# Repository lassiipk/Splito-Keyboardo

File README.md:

# Saim-Chan
Splito Keboardo, Made with ♥ by SAIM.  Named as サイムちゃん (Saimu-chan).

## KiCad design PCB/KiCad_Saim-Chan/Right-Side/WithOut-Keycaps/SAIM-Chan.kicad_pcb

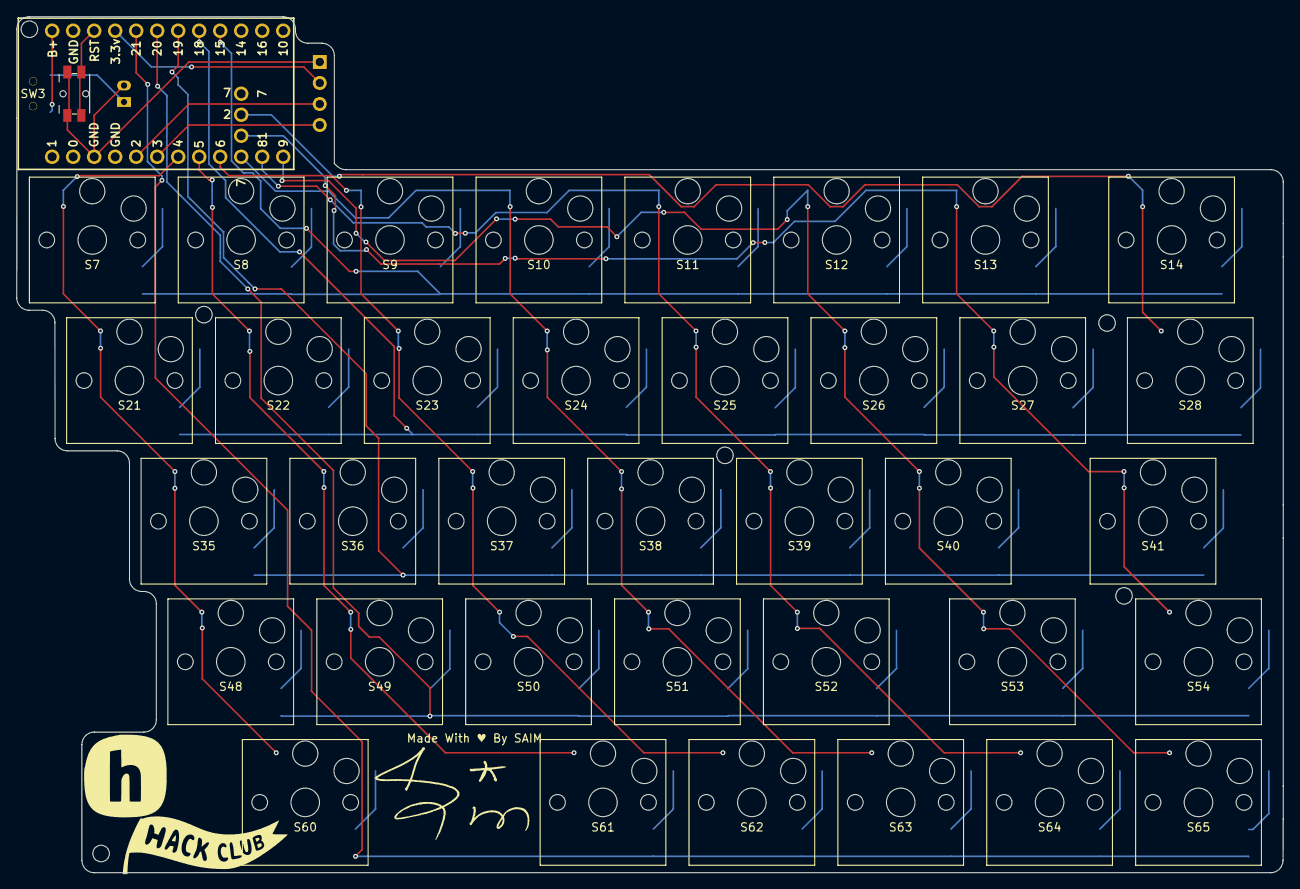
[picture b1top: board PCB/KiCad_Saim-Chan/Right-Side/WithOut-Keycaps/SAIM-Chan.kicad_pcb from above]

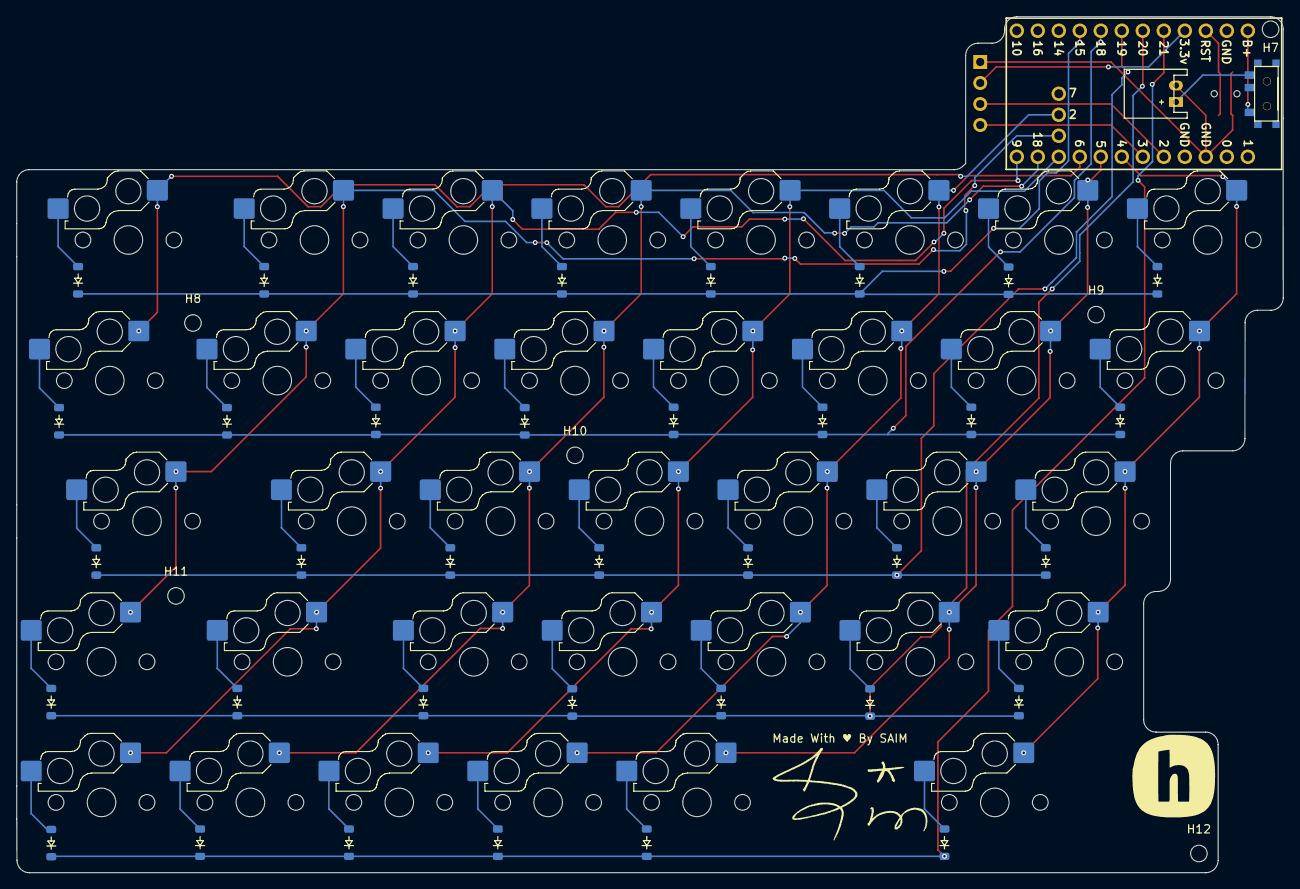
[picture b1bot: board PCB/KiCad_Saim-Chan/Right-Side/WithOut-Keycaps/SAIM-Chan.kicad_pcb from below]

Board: 2 copper layers, 153.1 x 103.5 mm, 83 parts (42 on the bottom side), 56 nets.

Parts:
D7, D8, D9, D10, D11, D12, D13, D14, D21, D22, D23, D24, D25, D26, D27, D28, D35, D36, D37, D38, D39, D40, D41, D48, D49, D50, D51, D52, D53, D54, D60, D61, D62, D63, D64, D65: Diode_SOD-123
Display_2: OLED_128x32
H7, H8, H9, H10, H11, H12: MountingScrew; MountingHole_2mm
J2: Conn_01x02; JST_PH_S2B-PH-K_02x2.00mm_Angled
S7, S8, S9, S10, S11, S12, S13, S21, S22, S23, S24, S25, S26, S27, S35, S36, S37, S38, S39, S40, S48, S49, S50, S51, S52, S54, S61, S62, S63, S64, S65: Hotswap_Choc_V1_1.00u
S14, S53: Hotswap_Choc_V1_1.50u
S28: Hotswap_Choc_V1_1.25u
S41: Hotswap_Choc_V1_1.75u
S60: Hotswap_Choc_V1_3.00u
SW2: SW_SPDT_312; SPDT_C128955
SW3: Switch; Panasonic_EVQPUL_EVQPUC
U2: Nice_Nano_V2

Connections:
COL0_R: S7.1, S21.1, S35.1, S48.1, S60.1, U2.7 (4)
COL1_R: S8.1, S22.1, S36.1, S49.1, S61.1, U2.8 (5)
COL2_R: S9.1, S23.1, S37.1, S50.1, S62.1, U2.9 (6)
COL3_R: S10.1, S24.1, S38.1, S51.1, S63.1, U2.10 (7)
COL4_R: S11.1, S25.1, S39.1, S52.1, S64.1, U2.11 (8)
COL5_R: S12.1, S26.1, S40.1, S53.1, S65.1, U2.12 (9)
COL6_R: S13.1, S27.1, S41.1, S54.1, U2.25 (1)
COL7_R: S14.1, S28.1, U2.26 (2)
GND_R: Display_2.1 (GND), J2.2, SW3.1, U2.3 (GND)
unnamed: D7.2 (A), S7.2
unnamed: D8.2 (A), S8.2
unnamed: D9.2 (A), S9.2
unnamed: D10.2 (A), S10.2
unnamed: D11.2 (A), S11.2
unnamed: D12.2 (A), S12.2
unnamed: D13.2 (A), S13.2
unnamed: D14.2 (A), S14.2
unnamed: D21.2 (A), S21.2
unnamed: D22.2 (A), S22.2
unnamed: D23.2 (A), S23.2
unnamed: D24.2 (A), S24.2
unnamed: D25.2 (A), S25.2
unnamed: D26.2 (A), S26.2
unnamed: D27.2 (A), S27.2
unnamed: D28.2 (A), S28.2
unnamed: D35.2 (A), S35.2
unnamed: D36.2 (A), S36.2
unnamed: D37.2 (A), S37.2
unnamed: D38.2 (A), S38.2
unnamed: D39.2 (A), S39.2
unnamed: D40.2 (A), S40.2
unnamed: D41.2 (A), S41.2
unnamed: D48.2 (A), S48.2
unnamed: D49.2 (A), S49.2
unnamed: D50.2 (A), S50.2
unnamed: D51.2 (A), S51.2
unnamed: D52.2 (A), S52.2
unnamed: D53.2 (A), S53.2
unnamed: D54.2 (A), S54.2
unnamed: D60.2 (A), S60.2
unnamed: D61.2 (A), S61.2
unnamed: D62.2 (A), S62.2
unnamed: D63.2 (A), S63.2
unnamed: D64.2 (A), S64.2
unnamed: D65.2 (A), S65.2
unnamed: J2.1, SW2.3 (A)
unnamed: SW2.1 (B), U2.24 (B+)
ROW0_R: D7.1 (K), D8.1 (K), D9.1 (K), D10.1 (K), D11.1 (K), D12.1 (K), D13.1 (K), D14.1 (K), U2.16 (15)
ROW1_R: D21.1 (K), D22.1 (K), D23.1 (K), D24.1 (K), D25.1 (K), D26.1 (K), D27.1 (K), D28.1 (K), U2.17 (18)
ROW2_R: D35.1 (K), D36.1 (K), D37.1 (K), D38.1 (K), D39.1 (K), D40.1 (K), D41.1 (K), U2.18 (19)
ROW3_R: D48.1 (K), D49.1 (K), D50.1 (K), D51.1 (K), D52.1 (K), D53.1 (K), D54.1 (K), U2.19 (20)
ROW4_R: D60.1 (K), D61.1 (K), D62.1 (K), D63.1 (K), D64.1 (K), D65.1 (K), U2.20 (21)
RST_R: SW3.2, U2.22 (RST)
SCL_R: Display_2.3 (SCL), U2.5 (2)
SDA_R: Display_2.4 (SDA), U2.6 (3)
VCC_R: Display_2.2 (VCC), U2.21 (3.3v)

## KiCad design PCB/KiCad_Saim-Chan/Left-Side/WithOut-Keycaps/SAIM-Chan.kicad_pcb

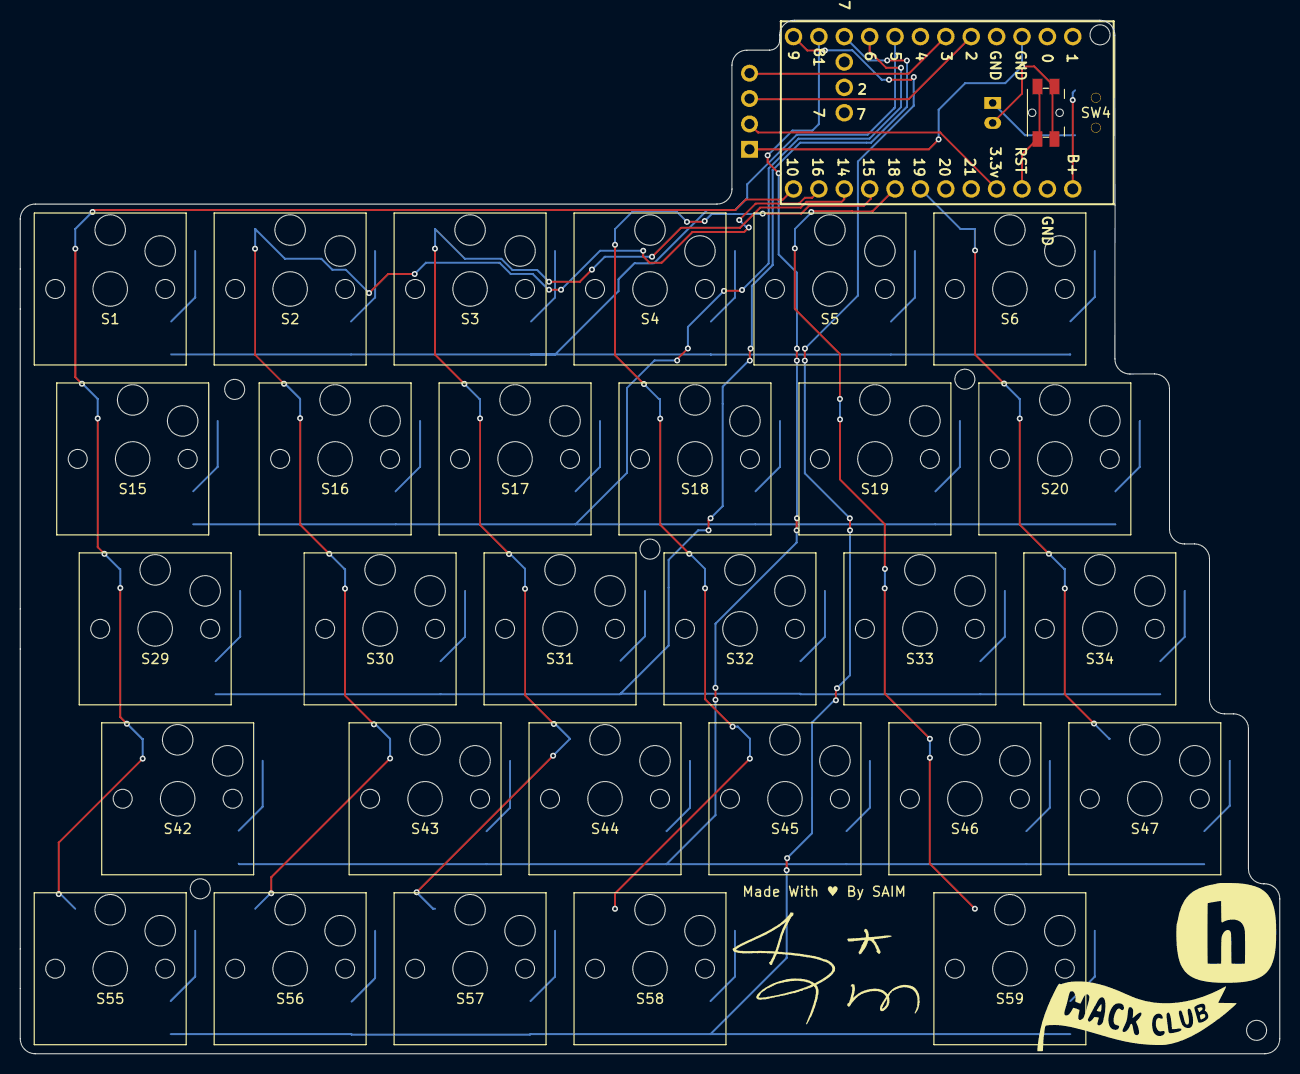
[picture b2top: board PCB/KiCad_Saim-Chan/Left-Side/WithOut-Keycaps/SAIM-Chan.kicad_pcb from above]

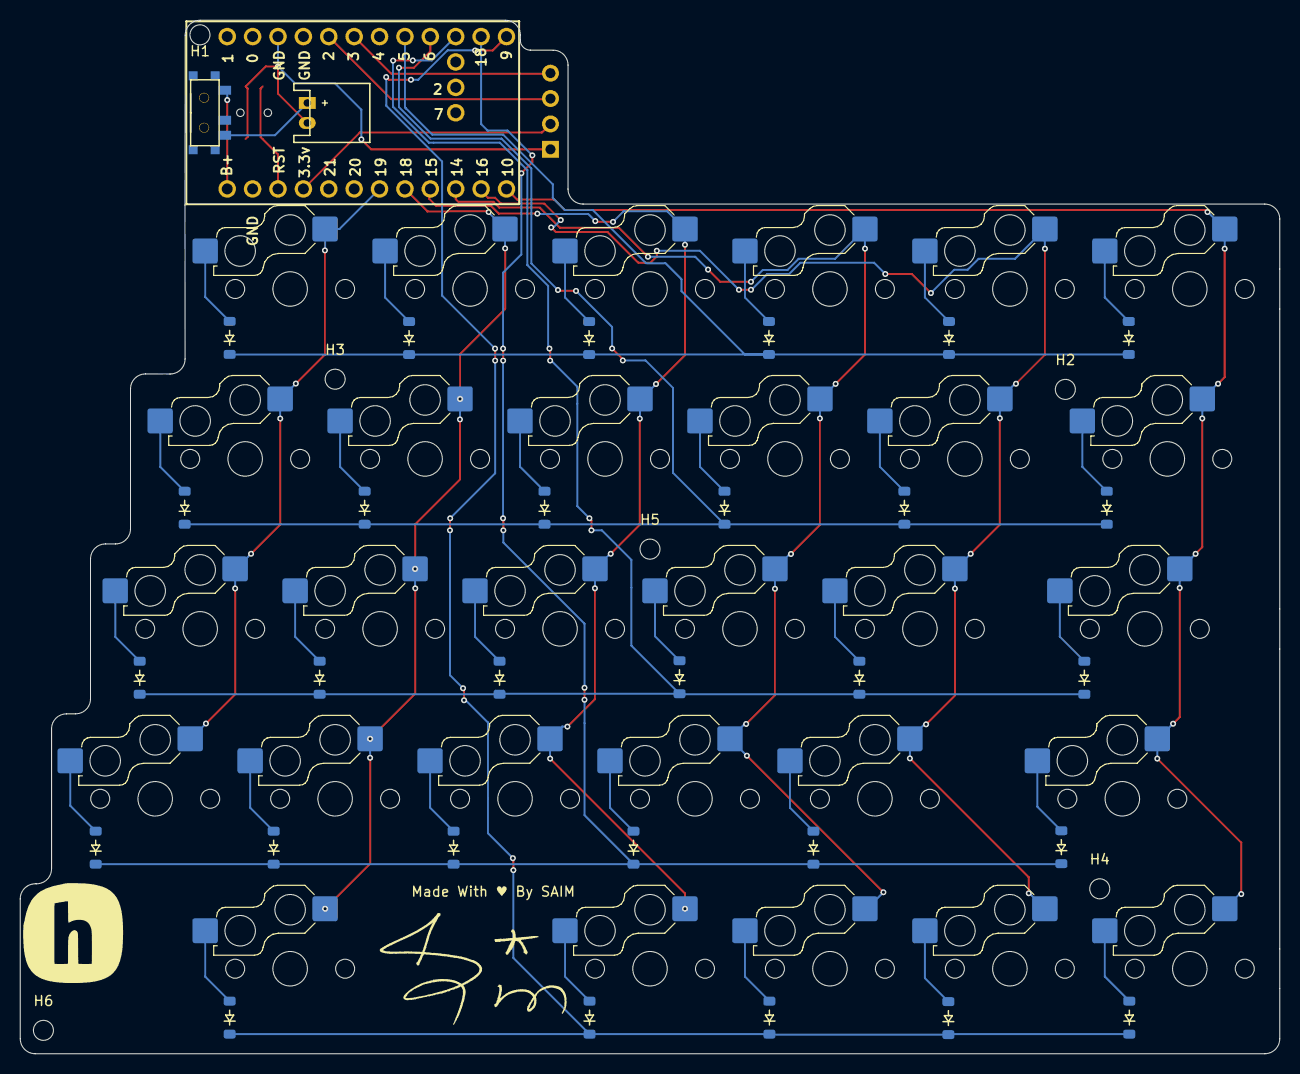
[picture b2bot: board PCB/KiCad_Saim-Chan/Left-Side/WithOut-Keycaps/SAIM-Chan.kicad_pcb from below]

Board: 2 copper layers, 126.0 x 103.4 mm, 69 parts (34 on the bottom side), 47 nets.

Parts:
D1, D2, D3, D4, D5, D6, D15, D16, D17, D18, D19, D20, D29, D30, D31, D32, D33, D34, D42, D43, D44, D45, D46, D47, D55, D56, D57, D58, D59: Diode_SOD-123
Display_1: OLED_128x32
H1, H2, H3, H4, H5, H6: MountingScrew; MountingHole_2mm
J1: Conn_01x02; JST_PH_S2B-PH-K_02x2.00mm_Angled
S1, S2, S3, S4, S5, S6, S16, S17, S18, S19, S20, S30, S31, S32, S33, S34, S43, S44, S45, S46, S47, S55, S56, S57, S58: Hotswap_Choc_V1_1.00u
S15: Hotswap_Choc_V1_1.25u
S29: Hotswap_Choc_V1_1.50u
S42: Hotswap_Choc_V1_1.75u
S59: Hotswap_Choc_V1_3.00u
SW1: SW_SPDT_312; SPDT_C128955
SW4: Switch; Panasonic_EVQPUL_EVQPUC
U1: Nice_Nano_V2

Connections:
COL0_L: S1.1, S15.1, S29.1, S42.1, S55.1, U1.13 (10)
COL1_L: S2.1, S16.1, S30.1, S43.1, S56.1, U1.14 (16)
COL2_L: S3.1, S17.1, S31.1, S44.1, S57.1, U1.15 (14)
COL3_L: S4.1, S18.1, S32.1, S45.1, S58.1, U1.16 (15)
COL4_L: S5.1, S19.1, S33.1, S46.1, S59.1, U1.17 (18)
COL5_L: S6.1, S20.1, S34.1, S47.1, U1.18 (19)
GND_L: Display_1.1 (GND), J1.2, SW4.1, U1.3 (GND)
unnamed: D1.2 (A), S1.2
unnamed: D2.2 (A), S2.2
unnamed: D3.2 (A), S3.2
unnamed: D4.2 (A), S4.2
unnamed: D5.2 (A), S5.2
unnamed: D6.2 (A), S6.2
unnamed: D15.2 (A), S15.2
unnamed: D16.2 (A), S16.2
unnamed: D17.2 (A), S17.2
unnamed: D18.2 (A), S18.2
unnamed: D19.2 (A), S19.2
unnamed: D20.2 (A), S20.2
unnamed: D29.2 (A), S29.2
unnamed: D30.2 (A), S30.2
unnamed: D31.2 (A), S31.2
unnamed: D32.2 (A), S32.2
unnamed: D33.2 (A), S33.2
unnamed: D34.2 (A), S34.2
unnamed: D42.2 (A), S42.2
unnamed: D43.2 (A), S43.2
unnamed: D44.2 (A), S44.2
unnamed: D45.2 (A), S45.2
unnamed: D46.2 (A), S46.2
unnamed: D47.2 (A), S47.2
unnamed: D55.2 (A), S55.2
unnamed: D56.2 (A), S56.2
unnamed: D57.2 (A), S57.2
unnamed: D58.2 (A), S58.2
unnamed: D59.2 (A), S59.2
unnamed: J1.1, SW1.3 (A)
unnamed: SW1.1 (B), U1.24 (B+)
ROW0_L: D1.1 (K), D2.1 (K), D3.1 (K), D4.1 (K), D5.1 (K), D6.1 (K), U1.8 (5)
ROW1_L: D15.1 (K), D16.1 (K), D17.1 (K), D18.1 (K), D19.1 (K), D20.1 (K), U1.9 (6)
ROW2_L: D29.1 (K), D30.1 (K), D31.1 (K), D32.1 (K), D33.1 (K), D34.1 (K), U1.10 (7)
ROW3_L: D42.1 (K), D43.1 (K), D44.1 (K), D45.1 (K), D46.1 (K), D47.1 (K), U1.11 (8)
ROW4_L: D55.1 (K), D56.1 (K), D57.1 (K), D58.1 (K), D59.1 (K), U1.12 (9)
RST_L: SW4.2, U1.22 (RST)
SCL_L: Display_1.3 (SCL), U1.5 (2)
SDA_L: Display_1.4 (SDA), U1.6 (3)
VCC_L: Display_1.2 (VCC), U1.21 (3.3v)

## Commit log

2026-03-29 First Commint
2026-04-15 Uploaded
